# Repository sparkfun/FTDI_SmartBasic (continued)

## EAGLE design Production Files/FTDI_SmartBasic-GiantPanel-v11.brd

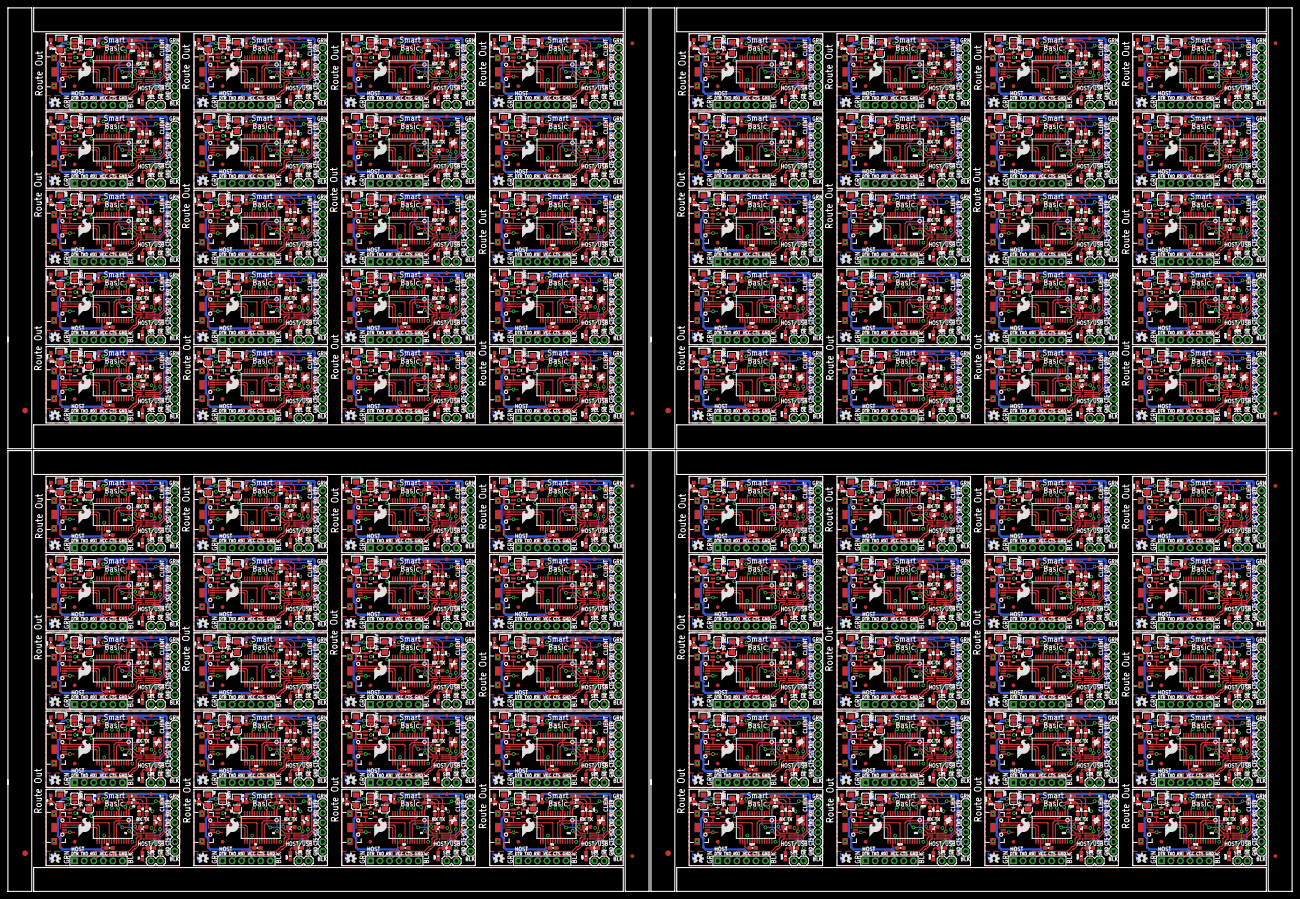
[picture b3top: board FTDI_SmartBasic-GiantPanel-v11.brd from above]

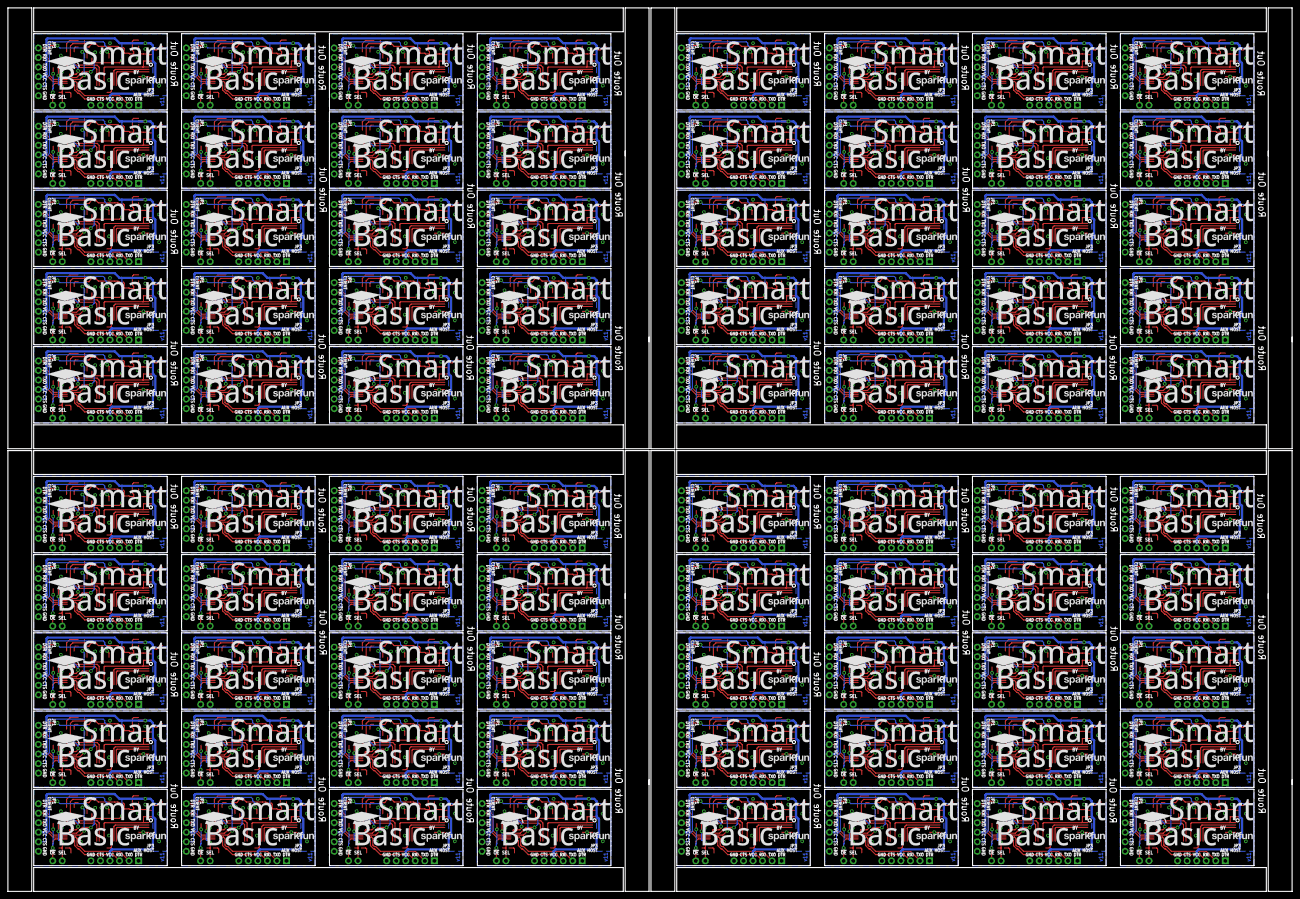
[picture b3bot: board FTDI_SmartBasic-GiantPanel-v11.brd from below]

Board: 2 copper layers, 341.9 x 235.2 mm, 2252 parts (160 on the bottom side), 1840 nets.

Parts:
C1, C3, C8, C11, C14, C17, C20, C23, C26, C29, C32, C35, C38, C41, C44, C47, C50, C53, C56, C59, C62, C65, C68, C71, C74, C77, C80, C83, C86, C89, C92, C95, C98, C101, C104, C107, C110, C113, C116, C119, C122, C125, C128, C131, C134, C137, C140, C143, C146, C149, C152, C155, C158, C161, C164, C167, C170, C173, C176, C179, C182, C185, C188, C191, C194, C197, C200, C203, C206, C209, C212, C215, C218, C221, C224, C227, C230, C233, C236, C239, C242, C245, C248, C251, C254, C257, C260, C263, C266, C269, C272, C275, C278, C281, C284, C287, C290, C293, C296, C299, C302, C305, C308, C311, C314, C317, C320, C323, C326, C329, C332, C335, C338, C341, C344, C347, C350, C353, C356, C359, C362, C365, C368, C371, C374, C377, C380, C383, C386, C389, C392, C395, C398, C401, C404, C407, C410, C413, C416, C419, C422, C425, C428, C431, C434, C437, C440, C443, C446, C449, C452, C455, C458, C461, C464, C467, C470, C473, C476, C479: 10uF; EIA3216
C2, C4, C5, C6, C7, C9, C10, C12, C13, C15, C16, C18, C19, C21, C22, C24, C25, C27, C28, C30, C31, C33, C34, C36, C37, C39, C40, C42, C43, C45, C46, C48, C49, C51, C52, C54, C55, C57, C58, C60, C61, C63, C64, C66, C67, C69, C70, C72, C73, C75, C76, C78, C79, C81, C82, C84, C85, C87, C88, C90, C91, C93, C94, C96, C97, C99, C100, C102, C103, C105, C106, C108, C109, C111, C112, C114, C115, C117, C118, C120, C121, C123, C124, C126, C127, C129, C130, C132, C133, C135, C136, C138, C139, C141, C142, C144, C145, C147, C148, C150, C151, C153, C154, C156, C157, C159, C160, C162, C163, C165, C166, C168, C169, C171, C172, C174, C175, C177, C178, C180, C181, C183, C184, C186, C187, C189, C190, C192, C193, C195, C196, C198, C199, C201, C202, C204, C205, C207, C208, C210, C211, C213, C214, C216, C217, C219, C220, C222, C223, C225, C226, C228, C229, C231, C232, C234, C235, C237, C238, C240, C241, C243, C244, C246, C247, C249, C250, C252, C253, C255, C256, C258, C259, C261, C262, C264, C265, C267, C268, C270, C271, C273, C274, C276, C277, C279, C280, C282, C283, C285, C286, C288, C289, C291, C292, C294, C295, C297, C298, C300, C301, C303, C304, C306, C307, C309, C310, C312, C313, C315, C316, C318, C319, C321, C322, C324, C325, C327, C328, C330, C331, C333, C334, C336, C337, C339, C340, C342, C343, C345, C346, C348, C349, C351, C352, C354, C355, C357, C358, C360, C361, C363, C364, C366, C367, C369, C370, C372, C373, C375, C376, C378, C379, C381, C382, C384, C385, C387, C388, C390, C391, C393, C394, C396, C397, C399, C400, C402, C403, C405, C406, C408, C409, C411, C412, C414, C415, C417, C418, C420, C421, C423, C424, C426, C427, C429, C430, C432, C433, C435, C436, C438, C439, C441, C442, C444, C445, C447, C448, C450, C451, C453, C454, C456, C457, C459, C460, C462, C463, C465, C466, C468, C469, C471, C472, C474, C475, C477, C478, C480: 0.1uF; 0603-CAP
CLIENT, CLIENT1, CLIENT2, CLIENT3, CLIENT4, CLIENT5, CLIENT6, CLIENT7, CLIENT8, CLIENT9, CLIENT10, CLIENT11, CLIENT12, CLIENT13, CLIENT14, CLIENT15, CLIENT16, CLIENT17, CLIENT18, CLIENT19, CLIENT20, CLIENT21, CLIENT22, CLIENT23, CLIENT24, CLIENT25, CLIENT26, CLIENT27, CLIENT28, CLIENT29, CLIENT30, CLIENT31, CLIENT32, CLIENT33, CLIENT34, CLIENT35, CLIENT36, CLIENT37, CLIENT38, CLIENT39, CLIENT40, CLIENT41, CLIENT42, CLIENT43, CLIENT44, CLIENT45, CLIENT46, CLIENT47, CLIENT48, CLIENT49, CLIENT50, CLIENT51, CLIENT52, CLIENT53, CLIENT54, CLIENT55, CLIENT56, CLIENT57, CLIENT58, CLIENT59, CLIENT60, CLIENT61, CLIENT62, CLIENT63, CLIENT64, CLIENT65, CLIENT66, CLIENT67, CLIENT68, CLIENT69, CLIENT70, CLIENT71, CLIENT72, CLIENT73, CLIENT74, CLIENT75, CLIENT76, CLIENT77, CLIENT78, CLIENT79: FTDI_BASIC
D1, D3, D4, D6, D7, D9, D10, D12, D13, D15, D16, D18, D19, D21, D22, D24, D25, D27, D28, D30, D31, D33, D34, D36, D37, D39, D40, D42, D43, D45, D46, D48, D49, D51, D52, D54, D55, D57, D58, D60, D61, D63, D64, D66, D67, D69, D70, D72, D73, D75, D76, D78, D79, D81, D82, D84, D85, D87, D88, D90, D91, D93, D94, D96, D97, D99, D100, D102, D103, D105, D106, D108, D109, D111, D112, D114, D115, D117, D118, D120, D121, D123, D124, D126, D127, D129, D130, D132, D133, D135, D136, D138, D139, D141, D142, D144, D145, D147, D148, D150, D151, D153, D154, D156, D157, D159, D160, D162, D163, D165, D166, D168, D169, D171, D172, D174, D175, D177, D178, D180, D181, D183, D184, D186, D187, D189, D190, D192, D193, D195, D196, D198, D199, D201, D202, D204, D205, D207, D208, D210, D211, D213, D214, D216, D217, D219, D220, D222, D223, D225, D226, D228, D229, D231, D232, D234, D235, D237, D238, D240: GREEN; LED-0603
D2, D5, D8, D11, D14, D17, D20, D23, D26, D29, D32, D35, D38, D41, D44, D47, D50, D53, D56, D59, D62, D65, D68, D71, D74, D77, D80, D83, D86, D89, D92, D95, D98, D101, D104, D107, D110, D113, D116, D119, D122, D125, D128, D131, D134, D137, D140, D143, D146, D149, D152, D155, D158, D161, D164, D167, D170, D173, D176, D179, D182, D185, D188, D191, D194, D197, D200, D203, D206, D209, D212, D215, D218, D221, D224, D227, D230, D233, D236, D239: RED; LED-0603
E$1, E$4, E$9, E$12: FIDUCIAL-1.5X3
E$2, E$3, E$5, E$6, E$7, E$8, E$10, E$11: FIDUCIAL-1X2
FID1, FID2, FID3, FID4, FID5, FID6, FID7, FID8, FID9, FID10, FID11, FID12, FID13, FID14, FID15, FID16, FID17, FID18, FID19, FID20, FID21, FID22, FID23, FID24, FID25, FID26, FID27, FID28, FID29, FID30, FID31, FID32, FID33, FID34, FID35, FID36, FID37, FID38, FID39, FID40, FID41, FID42, FID43, FID44, FID45, FID46, FID47, FID48, FID49, FID50, FID51, FID52, FID53, FID54, FID55, FID56, FID57, FID58, FID59, FID60, FID61, FID62, FID63, FID64, FID65, FID66, FID67, FID68, FID69, FID70, FID71, FID72, FID73, FID74, FID75, FID76, FID77, FID78, FID79, FID80, FID81, FID82, FID83, FID84, FID85, FID86, FID87, FID88, FID89, FID90, FID91, FID92, FID93, FID94, FID95, FID96, FID97, FID98, FID99, FID100, FID101, FID102, FID103, FID104, FID105, FID106, FID107, FID108, FID109, FID110, FID111, FID112, FID113, FID114, FID115, FID116, FID117, FID118, FID119, FID120, FID121, FID122, FID123, FID124, FID125, FID126, FID127, FID128, FID129, FID130, FID131, FID132, FID133, FID134, FID135, FID136, FID137, FID138, FID139, FID140, FID141, FID142, FID143, FID144, FID145, FID146, FID147, FID148, FID149, FID150, FID151, FID152, FID153, FID154, FID155, FID156, FID157, FID158, FID159, FID160: FIDUCIAL1X2; FIDUCIAL-1X2
HOST, HOST1, HOST2, HOST3, HOST4, HOST5, HOST6, HOST7, HOST8, HOST9, HOST10, HOST11, HOST12, HOST13, HOST14, HOST15, HOST16, HOST17, HOST18, HOST19, HOST20, HOST21, HOST22, HOST23, HOST24, HOST25, HOST26, HOST27, HOST28, HOST29, HOST30, HOST31, HOST32, HOST33, HOST34, HOST35, HOST36, HOST37, HOST38, HOST39, HOST40, HOST41, HOST42, HOST43, HOST44, HOST45, HOST46, HOST47, HOST48, HOST49, HOST50, HOST51, HOST52, HOST53, HOST54, HOST55, HOST56, HOST57, HOST58, HOST59, HOST60, HOST61, HOST62, HOST63, HOST64, HOST65, HOST66, HOST67, HOST68, HOST69, HOST70, HOST71, HOST72, HOST73, HOST74, HOST75, HOST76, HOST77, HOST78, HOST79: FTDI_DEVICE_SIDE
JP1, JP4, JP5, JP7, JP9, JP11, JP13, JP15, JP17, JP19, JP21, JP23, JP25, JP27, JP29, JP31, JP33, JP35, JP37, JP39, JP41, JP43, JP45, JP47, JP49, JP51, JP53, JP55, JP57, JP59, JP61, JP63, JP65, JP67, JP69, JP71, JP73, JP75, JP77, JP79, JP81, JP83, JP85, JP87, JP89, JP91, JP93, JP95, JP97, JP99, JP101, JP103, JP105, JP107, JP109, JP111, JP113, JP115, JP117, JP119, JP121, JP123, JP125, JP127, JP129, JP131, JP133, JP135, JP137, JP139, JP141, JP143, JP145, JP147, JP149, JP151, JP153, JP155, JP157, JP159: USB Micro B; USB-B-MICRO-SMD_V03
JP2, JP3, JP6, JP8, JP10, JP12, JP14, JP16, JP18, JP20, JP22, JP24, JP26, JP28, JP30, JP32, JP34, JP36, JP38, JP40, JP42, JP44, JP46, JP48, JP50, JP52, JP54, JP56, JP58, JP60, JP62, JP64, JP66, JP68, JP70, JP72, JP74, JP76, JP78, JP80, JP82, JP84, JP86, JP88, JP90, JP92, JP94, JP96, JP98, JP100, JP102, JP104, JP106, JP108, JP110, JP112, JP114, JP116, JP118, JP120, JP122, JP124, JP126, JP128, JP130, JP132, JP134, JP136, JP138, JP140, JP142, JP144, JP146, JP148, JP150, JP152, JP154, JP156, JP158, JP160: M02PTH; 1X02
LOGO1, LOGO4, LOGO7, LOGO10, LOGO13, LOGO16, LOGO19, LOGO22, LOGO25, LOGO28, LOGO31, LOGO34, LOGO37, LOGO40, LOGO43, LOGO46, LOGO49, LOGO52, LOGO55, LOGO58, LOGO61, LOGO64, LOGO67, LOGO70, LOGO73, LOGO76, LOGO79, LOGO82, LOGO85, LOGO88, LOGO91, LOGO94, LOGO97, LOGO100, LOGO103, LOGO106, LOGO109, LOGO112, LOGO115, LOGO118, LOGO121, LOGO124, LOGO127, LOGO130, LOGO133, LOGO136, LOGO139, LOGO142, LOGO145, LOGO148, LOGO151, LOGO154, LOGO157, LOGO160, LOGO163, LOGO166, LOGO169, LOGO172, LOGO175, LOGO178, LOGO181, LOGO184, LOGO187, LOGO190, LOGO193, LOGO196, LOGO199, LOGO202, LOGO205, LOGO208, LOGO211, LOGO214, LOGO217, LOGO220, LOGO223, LOGO226, LOGO229, LOGO232, LOGO235, LOGO238: SFE_LOGO_NAME.1_INCH; SFE_LOGO_NAME_.1
LOGO2, LOGO6, LOGO9, LOGO12, LOGO15, LOGO18, LOGO21, LOGO24, LOGO27, LOGO30, LOGO33, LOGO36, LOGO39, LOGO42, LOGO45, LOGO48, LOGO51, LOGO54, LOGO57, LOGO60, LOGO63, LOGO66, LOGO69, LOGO72, LOGO75, LOGO78, LOGO81, LOGO84, LOGO87, LOGO90, LOGO93, LOGO96, LOGO99, LOGO102, LOGO105, LOGO108, LOGO111, LOGO114, LOGO117, LOGO120, LOGO123, LOGO126, LOGO129, LOGO132, LOGO135, LOGO138, LOGO141, LOGO144, LOGO147, LOGO150, LOGO153, LOGO156, LOGO159, LOGO162, LOGO165, LOGO168, LOGO171, LOGO174, LOGO177, LOGO180, LOGO183, LOGO186, LOGO189, LOGO192, LOGO195, LOGO198, LOGO201, LOGO204, LOGO207, LOGO210, LOGO213, LOGO216, LOGO219, LOGO222, LOGO225, LOGO228, LOGO231, LOGO234, LOGO237, LOGO240: SFE_LOGO_FLAME.2_INCH; SFE_LOGO_FLAME_.2
LOGO3, LOGO5, LOGO8, LOGO11, LOGO14, LOGO17, LOGO20, LOGO23, LOGO26, LOGO29, LOGO32, LOGO35, LOGO38, LOGO41, LOGO44, LOGO47, LOGO50, LOGO53, LOGO56, LOGO59, LOGO62, LOGO65, LOGO68, LOGO71, LOGO74, LOGO77, LOGO80, LOGO83, LOGO86, LOGO89, LOGO92, LOGO95, LOGO98, LOGO101, LOGO104, LOGO107, LOGO110, LOGO113, LOGO116, LOGO119, LOGO122, LOGO125, LOGO128, LOGO131, LOGO134, LOGO137, LOGO140, LOGO143, LOGO146, LOGO149, LOGO152, LOGO155, LOGO158, LOGO161, LOGO164, LOGO167, LOGO170, LOGO173, LOGO176, LOGO179, LOGO182, LOGO185, LOGO188, LOGO191, LOGO194, LOGO197, LOGO200, LOGO203, LOGO206, LOGO209, LOGO212, LOGO215, LOGO218, LOGO221, LOGO224, LOGO227, LOGO230, LOGO233, LOGO236, LOGO239: OSHW-LOGOS; OSHW-LOGO-S
R1, R2, R3, R5, R6, R7, R9, R10, R11, R12, R14, R15, R16, R17, R19, R20, R21, R22, R24, R25, R26, R27, R29, R30, R31, R32, R34, R35, R36, R37, R39, R40, R41, R42, R44, R45, R46, R47, R49, R50, R51, R52, R54, R55, R56, R57, R59, R60, R61, R62, R64, R65, R66, R67, R69, R70, R71, R72, R74, R75, R76, R77, R79, R80, R81, R82, R84, R85, R86, R87, R89, R90, R91, R92, R94, R95, R96, R97, R99, R100, R101, R102, R104, R105, R106, R107, R109, R110, R111, R112, R114, R115, R116, R117, R119, R120, R121, R122, R124, R125, R126, R127, R129, R130, R131, R132, R134, R135, R136, R137, R139, R140, R141, R142, R144, R145, R146, R147, R149, R150, R151, R152, R154, R155, R156, R157, R159, R160, R161, R162, R164, R165, R166, R167, R169, R170, R171, R172, R174, R175, R176, R177, R179, R180, R181, R182, R184, R185, R186, R187, R189, R190, R191, R192, R194, R195, R196, R197, R199, R200, R201, R202, R204, R205, R206, R207, R209, R210, R211, R212, R214, R215, R216, R217, R219, R220, R221, R222, R224, R225, R226, R227, R229, R230, R231, R232, R234, R235, R236, R237, R239, R240, R241, R242, R244, R245, R246, R247, R249, R250, R251, R252, R254, R255, R256, R257, R259, R260, R261, R262, R264, R265, R266, R267, R269, R270, R271, R272, R274, R275, R276, R277, R279, R280, R281, R282, R284, R285, R286, R287, R289, R290, R291, R292, R294, R295, R296, R297, R299, R300, R301, R302, R304, R305, R306, R307, R309, R310, R311, R312, R314, R315, R316, R317, R319, R320, R321, R322, R324, R325, R326, R327, R329, R330, R331, R332, R334, R335, R336, R337, R339, R340, R341, R342, R344, R345, R346, R347, R349, R350, R351, R352, R354, R355, R356, R357, R359, R360, R361, R362, R364, R365, R366, R367, R369, R370, R371, R372, R374, R375, R376, R377, R379, R380, R381, R382, R384, R385, R386, R387, R389, R390, R391, R392, R394, R395, R396, R397, R399, R400: 1K; 0603-RES
R4, R8, R13, R18, R23, R28, R33, R38, R43, R48, R53, R58, R63, R68, R73, R78, R83, R88, R93, R98, R103, R108, R113, R118, R123, R128, R133, R138, R143, R148, R153, R158, R163, R168, R173, R178, R183, R188, R193, R198, R203, R208, R213, R218, R223, R228, R233, R238, R243, R248, R253, R258, R263, R268, R273, R278, R283, R288, R293, R298, R303, R308, R313, R318, R323, R328, R333, R338, R343, R348, R353, R358, R363, R368, R373, R378, R383, R388, R393, R398: 10K; 0603-RES
SJ1, SJ2, SJ3, SJ4, SJ5, SJ6, SJ7, SJ8, SJ9, SJ10, SJ11, SJ12, SJ13, SJ14, SJ15, SJ16, SJ17, SJ18, SJ19, SJ20, SJ21, SJ22, SJ23, SJ24, SJ25, SJ26, SJ27, SJ28, SJ29, SJ30, SJ31, SJ32, SJ33, SJ34, SJ35, SJ36, SJ37, SJ38, SJ39, SJ40, SJ41, SJ42, SJ43, SJ44, SJ45, SJ46, SJ47, SJ48, SJ49, SJ50, SJ51, SJ52, SJ53, SJ54, SJ55, SJ56, SJ57, SJ58, SJ59, SJ60, SJ61, SJ62, SJ63, SJ64, SJ65, SJ66, SJ67, SJ68, SJ69, SJ70, SJ71, SJ72, SJ73, SJ74, SJ75, SJ76, SJ77, SJ78, SJ79, SJ80: JUMPER-PAD-3-2OF3_NC_BY_PASTE; PAD-JUMPER-3-2OF3_NC_BY_PASTE_YES_SILK_FULL_BOX
U1, U5, U8, U11, U14, U17, U20, U23, U26, U29, U32, U35, U38, U41, U44, U47, U50, U53, U56, U59, U62, U65, U68, U71, U74, U77, U80, U83, U86, U89, U92, U95, U98, U101, U104, U107, U110, U113, U116, U119, U122, U125, U128, U131, U134, U137, U140, U143, U146, U149, U152, U155, U158, U161, U164, U167, U170, U173, U176, U179, U182, U185, U188, U191, U194, U197, U200, U203, U206, U209, U212, U215, U218, U221, U224, U227, U230, U233, U236, U239: FT232RLSSOP; SSOP28DB
U2, U6, U9, U12, U15, U18, U21, U24, U27, U30, U33, U36, U39, U42, U45, U48, U51, U54, U57, U60, U63, U66, U69, U72, U75, U78, U81, U84, U87, U90, U93, U96, U99, U102, U105, U108, U111, U114, U117, U120, U123, U126, U129, U132, U135, U138, U141, U144, U147, U150, U153, U156, U159, U162, U165, U168, U171, U174, U177, U180, U183, U186, U189, U192, U195, U198, U201, U204, U207, U210, U213, U216, U219, U222, U225, U228, U231, U234, U237, U240: MIC5219 3.3V; SOT23-5
U3, U4, U7, U10, U13, U16, U19, U22, U25, U28, U31, U34, U37, U40, U43, U46, U49, U52, U55, U58, U61, U64, U67, U70, U73, U76, U79, U82, U85, U88, U91, U94, U97, U100, U103, U106, U109, U112, U115, U118, U121, U124, U127, U130, U133, U136, U139, U142, U145, U148, U151, U154, U157, U160, U163, U166, U169, U172, U175, U178, U181, U184, U187, U190, U193, U196, U199, U202, U205, U208, U211, U214, U217, U220, U223, U226, U229, U232, U235, U238: TS3USB221A; QFN-10-RSE
U$1, U$2, U$3, U$4, U$5, U$6, U$7, U$8, U$9, U$10, U$11, U$12, U$13, U$14, U$15, U$16, U$17, U$18, U$19, U$20, U$21, U$22, U$23, U$24, U$25, U$26, U$27, U$28, U$29, U$30, U$31, U$32, U$33, U$34, U$35, U$36, U$37, U$38, U$39, U$40, U$41, U$42, U$43, U$44, U$45, U$46, U$47, U$48, U$49, U$50, U$51, U$52, U$53, U$54, U$55, U$56, U$57, U$58, U$59, U$60, U$61, U$62, U$63, U$64, U$65, U$66, U$67, U$68, U$69, U$70, U$71, U$72, U$73, U$74, U$75, U$76, U$77, U$78, U$79, U$80: SMART_BASIC_LOGO

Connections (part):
3.3V: C3.A, C5.1, C6.1, R1.2, R2.2, SJ1.1, U2.5, U3.10
3.3V1: C8.A, C10.1, C12.1, R6.2, R7.2, SJ2.1, U4.10, U6.5
3.3V2: C14.A, C16.1, C18.1, R11.2, R12.2, SJ3.1, U7.10, U9.5
3.3V3: C20.A, C22.1, C24.1, R16.2, R17.2, SJ4.1, U10.10, U12.5
3.3V4: C26.A, C28.1, C30.1, R21.2, R22.2, SJ5.1, U13.10, U15.5
3.3V5: C32.A, C34.1, C36.1, R26.2, R27.2, SJ6.1, U16.10, U18.5
3.3V6: C38.A, C40.1, C42.1, R31.2, R32.2, SJ7.1, U19.10, U21.5
3.3V7: C44.A, C46.1, C48.1, R36.2, R37.2, SJ8.1, U22.10, U24.5
3.3V8: C50.A, C52.1, C54.1, R41.2, R42.2, SJ9.1, U25.10, U27.5
3.3V9: C56.A, C58.1, C60.1, R46.2, R47.2, SJ10.1, U28.10, U30.5
3.3V10: C62.A, C64.1, C66.1, R51.2, R52.2, SJ11.1, U31.10, U33.5
3.3V11: C68.A, C70.1, C72.1, R56.2, R57.2, SJ12.1, U34.10, U36.5
3.3V12: C74.A, C76.1, C78.1, R61.2, R62.2, SJ13.1, U37.10, U39.5
3.3V13: C80.A, C82.1, C84.1, R66.2, R67.2, SJ14.1, U40.10, U42.5
3.3V14: C86.A, C88.1, C90.1, R71.2, R72.2, SJ15.1, U43.10, U45.5
3.3V15: C92.A, C94.1, C96.1, R76.2, R77.2, SJ16.1, U46.10, U48.5
3.3V16: C98.A, C100.1, C102.1, R81.2, R82.2, SJ17.1, U49.10, U51.5
3.3V17: C104.A, C106.1, C108.1, R86.2, R87.2, SJ18.1, U52.10, U54.5
3.3V18: C110.A, C112.1, C114.1, R91.2, R92.2, SJ19.1, U55.10, U57.5
3.3V19: C116.A, C118.1, C120.1, R96.2, R97.2, SJ20.1, U58.10, U60.5
3.3V20: C122.A, C124.1, C126.1, R101.2, R102.2, SJ21.1, U61.10, U63.5
3.3V21: C128.A, C130.1, C132.1, R106.2, R107.2, SJ22.1, U64.10, U66.5
3.3V22: C134.A, C136.1, C138.1, R111.2, R112.2, SJ23.1, U67.10, U69.5
3.3V23: C140.A, C142.1, C144.1, R116.2, R117.2, SJ24.1, U70.10, U72.5
3.3V24: C146.A, C148.1, C150.1, R121.2, R122.2, SJ25.1, U73.10, U75.5
3.3V25: C152.A, C154.1, C156.1, R126.2, R127.2, SJ26.1, U76.10, U78.5
3.3V26: C158.A, C160.1, C162.1, R131.2, R132.2, SJ27.1, U79.10, U81.5
3.3V27: C164.A, C166.1, C168.1, R136.2, R137.2, SJ28.1, U82.10, U84.5
3.3V28: C170.A, C172.1, C174.1, R141.2, R142.2, SJ29.1, U85.10, U87.5
3.3V29: C176.A, C178.1, C180.1, R146.2, R147.2, SJ30.1, U88.10, U90.5
3.3V30: C182.A, C184.1, C186.1, R151.2, R152.2, SJ31.1, U91.10, U93.5
3.3V31: C188.A, C190.1, C192.1, R156.2, R157.2, SJ32.1, U94.10, U96.5
3.3V32: C194.A, C196.1, C198.1, R161.2, R162.2, SJ33.1, U97.10, U99.5
3.3V33: C200.A, C202.1, C204.1, R166.2, R167.2, SJ34.1, U100.10, U102.5
3.3V34: C206.A, C208.1, C210.1, R171.2, R172.2, SJ35.1, U103.10, U105.5
3.3V35: C212.A, C214.1, C216.1, R176.2, R177.2, SJ36.1, U106.10, U108.5
3.3V36: C218.A, C220.1, C222.1, R181.2, R182.2, SJ37.1, U109.10, U111.5
3.3V37: C224.A, C226.1, C228.1, R186.2, R187.2, SJ38.1, U112.10, U114.5
3.3V38: C230.A, C232.1, C234.1, R191.2, R192.2, SJ39.1, U115.10, U117.5
3.3V39: C236.A, C238.1, C240.1, R196.2, R197.2, SJ40.1, U118.10, U120.5
3.3V40: C242.A, C244.1, C246.1, R201.2, R202.2, SJ41.1, U121.10, U123.5
3.3V41: C248.A, C250.1, C252.1, R206.2, R207.2, SJ42.1, U124.10, U126.5
3.3V42: C254.A, C256.1, C258.1, R211.2, R212.2, SJ43.1, U127.10, U129.5
3.3V43: C260.A, C262.1, C264.1, R216.2, R217.2, SJ44.1, U130.10, U132.5
3.3V44: C266.A, C268.1, C270.1, R221.2, R222.2, SJ45.1, U133.10, U135.5
3.3V45: C272.A, C274.1, C276.1, R226.2, R227.2, SJ46.1, U136.10, U138.5
3.3V46: C278.A, C280.1, C282.1, R231.2, R232.2, SJ47.1, U139.10, U141.5
3.3V47: C284.A, C286.1, C288.1, R236.2, R237.2, SJ48.1, U142.10, U144.5
3.3V48: C290.A, C292.1, C294.1, R241.2, R242.2, SJ49.1, U145.10, U147.5
3.3V49: C296.A, C298.1, C300.1, R246.2, R247.2, SJ50.1, U148.10, U150.5
3.3V50: C302.A, C304.1, C306.1, R251.2, R252.2, SJ51.1, U151.10, U153.5
3.3V51: C308.A, C310.1, C312.1, R256.2, R257.2, SJ52.1, U154.10, U156.5
3.3V52: C314.A, C316.1, C318.1, R261.2, R262.2, SJ53.1, U157.10, U159.5
3.3V53: C320.A, C322.1, C324.1, R266.2, R267.2, SJ54.1, U160.10, U162.5
3.3V54: C326.A, C328.1, C330.1, R271.2, R272.2, SJ55.1, U163.10, U165.5
3.3V55: C332.A, C334.1, C336.1, R276.2, R277.2, SJ56.1, U166.10, U168.5
3.3V56: C338.A, C340.1, C342.1, R281.2, R282.2, SJ57.1, U169.10, U171.5
3.3V57: C344.A, C346.1, C348.1, R286.2, R287.2, SJ58.1, U172.10, U174.5
3.3V58: C350.A, C352.1, C354.1, R291.2, R292.2, SJ59.1, U175.10, U177.5
3.3V59: C356.A, C358.1, C360.1, R296.2, R297.2, SJ60.1, U178.10, U180.5
3.3V60: C362.A, C364.1, C366.1, R301.2, R302.2, SJ61.1, U181.10, U183.5
3.3V61: C368.A, C370.1, C372.1, R306.2, R307.2, SJ62.1, U184.10, U186.5
3.3V62: C374.A, C376.1, C378.1, R311.2, R312.2, SJ63.1, U187.10, U189.5
3.3V63: C380.A, C382.1, C384.1, R316.2, R317.2, SJ64.1, U190.10, U192.5
3.3V64: C386.A, C388.1, C390.1, R321.2, R322.2, SJ65.1, U193.10, U195.5
3.3V65: C392.A, C394.1, C396.1, R326.2, R327.2, SJ66.1, U196.10, U198.5
3.3V66: C398.A, C400.1, C402.1, R331.2, R332.2, SJ67.1, U199.10, U201.5
3.3V67: C404.A, C406.1, C408.1, R336.2, R337.2, SJ68.1, U202.10, U204.5
3.3V68: C410.A, C412.1, C414.1, R341.2, R342.2, SJ69.1, U205.10, U207.5
3.3V69: C416.A, C418.1, C420.1, R346.2, R347.2, SJ70.1, U208.10, U210.5
3.3V70: C422.A, C424.1, C426.1, R351.2, R352.2, SJ71.1, U211.10, U213.5
3.3V71: C428.A, C430.1, C432.1, R356.2, R357.2, SJ72.1, U214.10, U216.5
3.3V72: C434.A, C436.1, C438.1, R361.2, R362.2, SJ73.1, U217.10, U219.5
3.3V73: C440.A, C442.1, C444.1, R366.2, R367.2, SJ74.1, U220.10, U222.5
3.3V74: C446.A, C448.1, C450.1, R371.2, R372.2, SJ75.1, U223.10, U225.5
3.3V75: C452.A, C454.1, C456.1, R376.2, R377.2, SJ76.1, U226.10, U228.5
3.3V76: C458.A, C460.1, C462.1, R381.2, R382.2, SJ77.1, U229.10, U231.5
3.3V77: C464.A, C466.1, C468.1, R386.2, R387.2, SJ78.1, U232.10, U234.5
3.3V78: C470.A, C472.1, C474.1, R391.2, R392.2, SJ79.1, U235.10, U237.5
3.3V79: C476.A, C478.1, C480.1, R396.2, R397.2, SJ80.1, U238.10, U240.5
5V: C1.A, C2.1, JP4.VBUS1, SJ1.3, U1.20, U2.1, U2.3
5V1: C7.1, C11.A, JP1.VBUS1, SJ2.3, U5.20, U6.1, U6.3
5V2: C13.1, C17.A, JP5.VBUS1, SJ3.3, U8.20, U9.1, U9.3
5V3: C19.1, C23.A, JP7.VBUS1, SJ4.3, U11.20, U12.1, U12.3
5V4: C25.1, C29.A, JP9.VBUS1, SJ5.3, U14.20, U15.1, U15.3
5V5: C31.1, C35.A, JP11.VBUS1, SJ6.3, U17.20, U18.1, U18.3
5V6: C37.1, C41.A, JP13.VBUS1, SJ7.3, U20.20, U21.1, U21.3
5V7: C43.1, C47.A, JP15.VBUS1, SJ8.3, U23.20, U24.1, U24.3
5V8: C49.1, C53.A, JP17.VBUS1, SJ9.3, U26.20, U27.1, U27.3
5V9: C55.1, C59.A, JP19.VBUS1, SJ10.3, U29.20, U30.1, U30.3
5V10: C61.1, C65.A, JP21.VBUS1, SJ11.3, U32.20, U33.1, U33.3
5V11: C67.1, C71.A, JP23.VBUS1, SJ12.3, U35.20, U36.1, U36.3
5V12: C73.1, C77.A, JP25.VBUS1, SJ13.3, U38.20, U39.1, U39.3
5V13: C79.1, C83.A, JP27.VBUS1, SJ14.3, U41.20, U42.1, U42.3
5V14: C85.1, C89.A, JP29.VBUS1, SJ15.3, U44.20, U45.1, U45.3
5V15: C91.1, C95.A, JP31.VBUS1, SJ16.3, U47.20, U48.1, U48.3
5V16: C97.1, C101.A, JP33.VBUS1, SJ17.3, U50.20, U51.1, U51.3
5V17: C103.1, C107.A, JP35.VBUS1, SJ18.3, U53.20, U54.1, U54.3
5V18: C109.1, C113.A, JP37.VBUS1, SJ19.3, U56.20, U57.1, U57.3
5V19: C115.1, C119.A, JP39.VBUS1, SJ20.3, U59.20, U60.1, U60.3
5V20: C121.1, C125.A, JP41.VBUS1, SJ21.3, U62.20, U63.1, U63.3
5V21: C127.1, C131.A, JP43.VBUS1, SJ22.3, U65.20, U66.1, U66.3
5V22: C133.1, C137.A, JP45.VBUS1, SJ23.3, U68.20, U69.1, U69.3
5V23: C139.1, C143.A, JP47.VBUS1, SJ24.3, U71.20, U72.1, U72.3
5V24: C145.1, C149.A, JP49.VBUS1, SJ25.3, U74.20, U75.1, U75.3
5V25: C151.1, C155.A, JP51.VBUS1, SJ26.3, U77.20, U78.1, U78.3
5V26: C157.1, C161.A, JP53.VBUS1, SJ27.3, U80.20, U81.1, U81.3
5V27: C163.1, C167.A, JP55.VBUS1, SJ28.3, U83.20, U84.1, U84.3
5V28: C169.1, C173.A, JP57.VBUS1, SJ29.3, U86.20, U87.1, U87.3
5V29: C175.1, C179.A, JP59.VBUS1, SJ30.3, U89.20, U90.1, U90.3
5V30: C181.1, C185.A, JP61.VBUS1, SJ31.3, U92.20, U93.1, U93.3
5V31: C187.1, C191.A, JP63.VBUS1, SJ32.3, U95.20, U96.1, U96.3
5V32: C193.1, C197.A, JP65.VBUS1, SJ33.3, U98.20, U99.1, U99.3
5V33: C199.1, C203.A, JP67.VBUS1, SJ34.3, U101.20, U102.1, U102.3
5V34: C205.1, C209.A, JP69.VBUS1, SJ35.3, U104.20, U105.1, U105.3
5V35: C211.1, C215.A, JP71.VBUS1, SJ36.3, U107.20, U108.1, U108.3
5V36: C217.1, C221.A, JP73.VBUS1, SJ37.3, U110.20, U111.1, U111.3
5V37: C223.1, C227.A, JP75.VBUS1, SJ38.3, U113.20, U114.1, U114.3
5V38: C229.1, C233.A, JP77.VBUS1, SJ39.3, U116.20, U117.1, U117.3
5V39: C235.1, C239.A, JP79.VBUS1, SJ40.3, U119.20, U120.1, U120.3
5V40: C241.1, C245.A, JP81.VBUS1, SJ41.3, U122.20, U123.1, U123.3
5V41: C247.1, C251.A, JP83.VBUS1, SJ42.3, U125.20, U126.1, U126.3
5V42: C253.1, C257.A, JP85.VBUS1, SJ43.3, U128.20, U129.1, U129.3
5V43: C259.1, C263.A, JP87.VBUS1, SJ44.3, U131.20, U132.1, U132.3
5V44: C265.1, C269.A, JP89.VBUS1, SJ45.3, U134.20, U135.1, U135.3
5V45: C271.1, C275.A, JP91.VBUS1, SJ46.3, U137.20, U138.1, U138.3
5V46: C277.1, C281.A, JP93.VBUS1, SJ47.3, U140.20, U141.1, U141.3
5V47: C283.1, C287.A, JP95.VBUS1, SJ48.3, U143.20, U144.1, U144.3
5V48: C289.1, C293.A, JP97.VBUS1, SJ49.3, U146.20, U147.1, U147.3
5V49: C295.1, C299.A, JP99.VBUS1, SJ50.3, U149.20, U150.1, U150.3
5V50: C301.1, C305.A, JP101.VBUS1, SJ51.3, U152.20, U153.1, U153.3
5V51: C307.1, C311.A, JP103.VBUS1, SJ52.3, U155.20, U156.1, U156.3
5V52: C313.1, C317.A, JP105.VBUS1, SJ53.3, U158.20, U159.1, U159.3
5V53: C319.1, C323.A, JP107.VBUS1, SJ54.3, U161.20, U162.1, U162.3
5V54: C325.1, C329.A, JP109.VBUS1, SJ55.3, U164.20, U165.1, U165.3
5V55: C331.1, C335.A, JP111.VBUS1, SJ56.3, U167.20, U168.1, U168.3
5V56: C337.1, C341.A, JP113.VBUS1, SJ57.3, U170.20, U171.1, U171.3
5V57: C343.1, C347.A, JP115.VBUS1, SJ58.3, U173.20, U174.1, U174.3
5V58: C349.1, C353.A, JP117.VBUS1, SJ59.3, U176.20, U177.1, U177.3
5V59: C355.1, C359.A, JP119.VBUS1, SJ60.3, U179.20, U180.1, U180.3
5V60: C361.1, C365.A, JP121.VBUS1, SJ61.3, U182.20, U183.1, U183.3
5V61: C367.1, C371.A, JP123.VBUS1, SJ62.3, U185.20, U186.1, U186.3
5V62: C373.1, C377.A, JP125.VBUS1, SJ63.3, U188.20, U189.1, U189.3
5V63: C379.1, C383.A, JP127.VBUS1, SJ64.3, U191.20, U192.1, U192.3
5V64: C385.1, C389.A, JP129.VBUS1, SJ65.3, U194.20, U195.1, U195.3
5V65: C391.1, C395.A, JP131.VBUS1, SJ66.3, U197.20, U198.1, U198.3
5V66: C397.1, C401.A, JP133.VBUS1, SJ67.3, U200.20, U201.1, U201.3
5V67: C403.1, C407.A, JP135.VBUS1, SJ68.3, U203.20, U204.1, U204.3
5V68: C409.1, C413.A, JP137.VBUS1, SJ69.3, U206.20, U207.1, U207.3
5V69: C415.1, C419.A, JP139.VBUS1, SJ70.3, U209.20, U210.1, U210.3
5V70: C421.1, C425.A, JP141.VBUS1, SJ71.3, U212.20, U213.1, U213.3
5V71: C427.1, C431.A, JP143.VBUS1, SJ72.3, U215.20, U216.1, U216.3
5V72: C433.1, C437.A, JP145.VBUS1, SJ73.3, U218.20, U219.1, U219.3
5V73: C439.1, C443.A, JP147.VBUS1, SJ74.3, U221.20, U222.1, U222.3
5V74: C445.1, C449.A, JP149.VBUS1, SJ75.3, U224.20, U225.1, U225.3
5V75: C451.1, C455.A, JP151.VBUS1, SJ76.3, U227.20, U228.1, U228.3
5V76: C457.1, C461.A, JP153.VBUS1, SJ77.3, U230.20, U231.1, U231.3
5V77: C463.1, C467.A, JP155.VBUS1, SJ78.3, U233.20, U234.1, U234.3
5V78: C469.1, C473.A, JP157.VBUS1, SJ79.3, U236.20, U237.1, U237.3
5V79: C475.1, C479.A, JP159.VBUS1, SJ80.3, U239.20, U240.1, U240.3
!OE: JP2.1, R4.1, U3.6
!OE1: JP3.1, R8.1, U4.6
!OE2: JP6.1, R13.1, U7.6
!OE3: JP8.1, R18.1, U10.6
!OE4: JP10.1, R23.1, U13.6
!OE5: JP12.1, R28.1, U16.6
!OE6: JP14.1, R33.1, U19.6
!OE7: JP16.1, R38.1, U22.6
!OE8: JP18.1, R43.1, U25.6
!OE9: JP20.1, R48.1, U28.6
!OE10: JP22.1, R53.1, U31.6
!OE11: JP24.1, R58.1, U34.6
!OE12: JP26.1, R63.1, U37.6
!OE13: JP28.1, R68.1, U40.6
!OE14: JP30.1, R73.1, U43.6
!OE15: JP32.1, R78.1, U46.6
!OE16: JP34.1, R83.1, U49.6
!OE17: JP36.1, R88.1, U52.6
!OE18: JP38.1, R93.1, U55.6
!OE19: JP40.1, R98.1, U58.6
!OE20: JP42.1, R103.1, U61.6
!OE21: JP44.1, R108.1, U64.6
!OE22: JP46.1, R113.1, U67.6
!OE23: JP48.1, R118.1, U70.6
!OE24: JP50.1, R123.1, U73.6
!OE25: JP52.1, R128.1, U76.6
!OE26: JP54.1, R133.1, U79.6
!OE27: JP56.1, R138.1, U82.6
!OE28: JP58.1, R143.1, U85.6
!OE29: JP60.1, R148.1, U88.6
!OE30: JP62.1, R153.1, U91.6
!OE31: JP64.1, R158.1, U94.6
!OE32: JP66.1, R163.1, U97.6
!OE33: JP68.1, R168.1, U100.6
!OE34: JP70.1, R173.1, U103.6
!OE35: JP72.1, R178.1, U106.6
!OE36: JP74.1, R183.1, U109.6
!OE37: JP76.1, R188.1, U112.6
!OE38: JP78.1, R193.1, U115.6
!OE39: JP80.1, R198.1, U118.6
!OE40: JP82.1, R203.1, U121.6
!OE41: JP84.1, R208.1, U124.6
!OE42: JP86.1, R213.1, U127.6
!OE43: JP88.1, R218.1, U130.6
!OE44: JP90.1, R223.1, U133.6
!OE45: JP92.1, R228.1, U136.6
!OE46: JP94.1, R233.1, U139.6
!OE47: JP96.1, R238.1, U142.6
!OE48: JP98.1, R243.1, U145.6
!OE49: JP100.1, R248.1, U148.6
!OE50: JP102.1, R253.1, U151.6
!OE51: JP104.1, R258.1, U154.6
!OE52: JP106.1, R263.1, U157.6
!OE53: JP108.1, R268.1, U160.6
!OE54: JP110.1, R273.1, U163.6
!OE55: JP112.1, R278.1, U166.6
!OE56: JP114.1, R283.1, U169.6
!OE57: JP116.1, R288.1, U172.6
!OE58: JP118.1, R293.1, U175.6
!OE59: JP120.1, R298.1, U178.6
!OE60: JP122.1, R303.1, U181.6
!OE61: JP124.1, R308.1, U184.6
!OE62: JP126.1, R313.1, U187.6
!OE63: JP128.1, R318.1, U190.6
!OE64: JP130.1, R323.1, U193.6
!OE65: JP132.1, R328.1, U196.6
!OE66: JP134.1, R333.1, U199.6
!OE67: JP136.1, R338.1, U202.6
!OE68: JP138.1, R343.1, U205.6
!OE69: JP140.1, R348.1, U208.6
!OE70: JP142.1, R353.1, U211.6
!OE71: JP144.1, R358.1, U214.6
!OE72: JP146.1, R363.1, U217.6
!OE73: JP148.1, R368.1, U220.6
!OE74: JP150.1, R373.1, U223.6
!OE75: JP152.1, R378.1, U226.6
!OE76: JP154.1, R383.1, U229.6
!OE77: JP156.1, R388.1, U232.6
!OE78: JP158.1, R393.1, U235.6
!OE79: JP160.1, R398.1, U238.6
CTS: CLIENT.CTS, U1.11
CTS1: CLIENT1.CTS, U5.11
CTS2: CLIENT2.CTS, U8.11
CTS3: CLIENT3.CTS, U11.11
CTS4: CLIENT4.CTS, U14.11
CTS5: CLIENT5.CTS, U17.11
CTS6: CLIENT6.CTS, U20.11
CTS7: CLIENT7.CTS, U23.11
CTS8: CLIENT8.CTS, U26.11
CTS9: CLIENT9.CTS, U29.11
CTS10: CLIENT10.CTS, U32.11
CTS11: CLIENT11.CTS, U35.11
CTS12: CLIENT12.CTS, U38.11
CTS13: CLIENT13.CTS, U41.11
CTS14: CLIENT14.CTS, U44.11
CTS15: CLIENT15.CTS, U47.11
CTS16: CLIENT16.CTS, U50.11
CTS17: CLIENT17.CTS, U53.11
CTS18: CLIENT18.CTS, U56.11
CTS19: CLIENT19.CTS, U59.11
CTS20: CLIENT20.CTS, U62.11
CTS21: CLIENT21.CTS, U65.11
CTS22: CLIENT22.CTS, U68.11
CTS23: CLIENT23.CTS, U71.11
CTS24: CLIENT24.CTS, U74.11
CTS25: CLIENT25.CTS, U77.11
CTS26: CLIENT26.CTS, U80.11
CTS27: CLIENT27.CTS, U83.11
CTS28: CLIENT28.CTS, U86.11
CTS29: CLIENT29.CTS, U89.11
CTS30: CLIENT30.CTS, U92.11
CTS31: CLIENT31.CTS, U95.11
CTS32: CLIENT32.CTS, U98.11
CTS33: CLIENT33.CTS, U101.11
CTS34: CLIENT34.CTS, U104.11
CTS35: CLIENT35.CTS, U107.11
CTS36: CLIENT36.CTS, U110.11
CTS37: CLIENT37.CTS, U113.11
CTS38: CLIENT38.CTS, U116.11
CTS39: CLIENT39.CTS, U119.11
CTS40: CLIENT40.CTS, U122.11
CTS41: CLIENT41.CTS, U125.11
CTS42: CLIENT42.CTS, U128.11
CTS43: CLIENT43.CTS, U131.11
CTS44: CLIENT44.CTS, U134.11
CTS45: CLIENT45.CTS, U137.11
CTS46: CLIENT46.CTS, U140.11
CTS47: CLIENT47.CTS, U143.11
CTS48: CLIENT48.CTS, U146.11
CTS49: CLIENT49.CTS, U149.11
CTS50: CLIENT50.CTS, U152.11
CTS51: CLIENT51.CTS, U155.11
CTS52: CLIENT52.CTS, U158.11
CTS53: CLIENT53.CTS, U161.11
CTS54: CLIENT54.CTS, U164.11
CTS55: CLIENT55.CTS, U167.11
CTS56: CLIENT56.CTS, U170.11
CTS57: CLIENT57.CTS, U173.11
CTS58: CLIENT58.CTS, U176.11
CTS59: CLIENT59.CTS, U179.11
CTS60: CLIENT60.CTS, U182.11
CTS61: CLIENT61.CTS, U185.11
CTS62: CLIENT62.CTS, U188.11
CTS63: CLIENT63.CTS, U191.11
CTS64: CLIENT64.CTS, U194.11
CTS65: CLIENT65.CTS, U197.11
CTS66: CLIENT66.CTS, U200.11
CTS67: CLIENT67.CTS, U203.11
CTS68: CLIENT68.CTS, U206.11
CTS69: CLIENT69.CTS, U209.11
CTS70: CLIENT70.CTS, U212.11
CTS71: CLIENT71.CTS, U215.11
CTS72: CLIENT72.CTS, U218.11
CTS73: CLIENT73.CTS, U221.11
CTS74: CLIENT74.CTS, U224.11
CTS75: CLIENT75.CTS, U227.11
CTS76: CLIENT76.CTS, U230.11
CTS77: CLIENT77.CTS, U233.11
CTS78: CLIENT78.CTS, U236.11
CTS79: CLIENT79.CTS, U239.11
DTR: CLIENT.DTR, U1.2
DTR1: CLIENT1.DTR, U5.2
DTR2: CLIENT2.DTR, U8.2
DTR3: CLIENT3.DTR, U11.2
DTR4: CLIENT4.DTR, U14.2
DTR5: CLIENT5.DTR, U17.2
DTR6: CLIENT6.DTR, U20.2
DTR7: CLIENT7.DTR, U23.2
DTR8: CLIENT8.DTR, U26.2
DTR9: CLIENT9.DTR, U29.2
DTR10: CLIENT10.DTR, U32.2
DTR11: CLIENT11.DTR, U35.2
DTR12: CLIENT12.DTR, U38.2
DTR13: CLIENT13.DTR, U41.2
DTR14: CLIENT14.DTR, U44.2
DTR15: CLIENT15.DTR, U47.2
DTR16: CLIENT16.DTR, U50.2
DTR17: CLIENT17.DTR, U53.2
DTR18: CLIENT18.DTR, U56.2
DTR19: CLIENT19.DTR, U59.2
DTR20: CLIENT20.DTR, U62.2
DTR21: CLIENT21.DTR, U65.2
DTR22: CLIENT22.DTR, U68.2
DTR23: CLIENT23.DTR, U71.2
DTR24: CLIENT24.DTR, U74.2
DTR25: CLIENT25.DTR, U77.2
DTR26: CLIENT26.DTR, U80.2
DTR27: CLIENT27.DTR, U83.2
DTR28: CLIENT28.DTR, U86.2
DTR29: CLIENT29.DTR, U89.2
DTR30: CLIENT30.DTR, U92.2
DTR31: CLIENT31.DTR, U95.2
DTR32: CLIENT32.DTR, U98.2
DTR33: CLIENT33.DTR, U101.2
DTR34: CLIENT34.DTR, U104.2
DTR35: CLIENT35.DTR, U107.2
DTR36: CLIENT36.DTR, U110.2
DTR37: CLIENT37.DTR, U113.2
DTR38: CLIENT38.DTR, U116.2
DTR39: CLIENT39.DTR, U119.2
DTR40: CLIENT40.DTR, U122.2
DTR41: CLIENT41.DTR, U125.2
DTR42: CLIENT42.DTR, U128.2
DTR43: CLIENT43.DTR, U131.2
DTR44: CLIENT44.DTR, U134.2
DTR45: CLIENT45.DTR, U137.2
DTR46: CLIENT46.DTR, U140.2
DTR47: CLIENT47.DTR, U143.2
DTR48: CLIENT48.DTR, U146.2
DTR49: CLIENT49.DTR, U149.2
DTR50: CLIENT50.DTR, U152.2
DTR51: CLIENT51.DTR, U155.2
DTR52: CLIENT52.DTR, U158.2
DTR53: CLIENT53.DTR, U161.2
DTR54: CLIENT54.DTR, U164.2
DTR55: CLIENT55.DTR, U167.2
DTR56: CLIENT56.DTR, U170.2
DTR57: CLIENT57.DTR, U173.2
DTR58: CLIENT58.DTR, U176.2
DTR59: CLIENT59.DTR, U179.2
DTR60: CLIENT60.DTR, U182.2
DTR61: CLIENT61.DTR, U185.2
DTR62: CLIENT62.DTR, U188.2
DTR63: CLIENT63.DTR, U191.2
DTR64: CLIENT64.DTR, U194.2
DTR65: CLIENT65.DTR, U197.2
DTR66: CLIENT66.DTR, U200.2
DTR67: CLIENT67.DTR, U203.2
DTR68: CLIENT68.DTR, U206.2
DTR69: CLIENT69.DTR, U209.2
DTR70: CLIENT70.DTR, U212.2
DTR71: CLIENT71.DTR, U215.2
DTR72: CLIENT72.DTR, U218.2
DTR73: CLIENT73.DTR, U221.2
DTR74: CLIENT74.DTR, U224.2
DTR75: CLIENT75.DTR, U227.2
DTR76: CLIENT76.DTR, U230.2
DTR77: CLIENT77.DTR, U233.2
DTR78: CLIENT78.DTR, U236.2
DTR79: CLIENT79.DTR, U239.2
GND: C1.C, C2.2, C3.C, C4.2, C5.2, C6.2, CLIENT.GND, HOST.P$6, JP4.GND1, R3.1, R4.2, R5.1, U1.7, U1.18, U1.21, U1.25, U1.26, U2.2, U3.5
GND1: C7.2, C8.C, C9.2, C10.2, C11.C, C12.2, CLIENT1.GND, HOST1.P$6, JP1.GND1, R8.2, R9.1, R10.1, U4.5, U5.7, U5.18, U5.21, U5.25, U5.26, U6.2
GND2: C13.2, C14.C, C15.2, C16.2, C17.C, C18.2, CLIENT2.GND, HOST2.P$6, JP5.GND1, R13.2, R14.1, R15.1, U7.5, U8.7, U8.18, U8.21, U8.25, U8.26, U9.2
GND3: C19.2, C20.C, C21.2, C22.2, C23.C, C24.2, CLIENT3.GND, HOST3.P$6, JP7.GND1, R18.2, R19.1, R20.1, U10.5, U11.7, U11.18, U11.21, U11.25, U11.26, U12.2
GND4: C25.2, C26.C, C27.2, C28.2, C29.C, C30.2, CLIENT4.GND, HOST4.P$6, JP9.GND1, R23.2, R24.1, R25.1, U13.5, U14.7, U14.18, U14.21, U14.25, U14.26, U15.2
GND5: C31.2, C32.C, C33.2, C34.2, C35.C, C36.2, CLIENT5.GND, HOST5.P$6, JP11.GND1, R28.2, R29.1, R30.1, U16.5, U17.7, U17.18, U17.21, U17.25, U17.26, U18.2
GND6: C37.2, C38.C, C39.2, C40.2, C41.C, C42.2, CLIENT6.GND, HOST6.P$6, JP13.GND1, R33.2, R34.1, R35.1, U19.5, U20.7, U20.18, U20.21, U20.25, U20.26, U21.2
GND7: C43.2, C44.C, C45.2, C46.2, C47.C, C48.2, CLIENT7.GND, HOST7.P$6, JP15.GND1, R38.2, R39.1, R40.1, U22.5, U23.7, U23.18, U23.21, U23.25, U23.26, U24.2
GND8: C49.2, C50.C, C51.2, C52.2, C53.C, C54.2, CLIENT8.GND, HOST8.P$6, JP17.GND1, R43.2, R44.1, R45.1, U25.5, U26.7, U26.18, U26.21, U26.25, U26.26, U27.2
GND9: C55.2, C56.C, C57.2, C58.2, C59.C, C60.2, CLIENT9.GND, HOST9.P$6, JP19.GND1, R48.2, R49.1, R50.1, U28.5, U29.7, U29.18, U29.21, U29.25, U29.26, U30.2
GND10: C61.2, C62.C, C63.2, C64.2, C65.C, C66.2, CLIENT10.GND, HOST10.P$6, JP21.GND1, R53.2, R54.1, R55.1, U31.5, U32.7, U32.18, U32.21, U32.25, U32.26, U33.2
GND11: C67.2, C68.C, C69.2, C70.2, C71.C, C72.2, CLIENT11.GND, HOST11.P$6, JP23.GND1, R58.2, R59.1, R60.1, U34.5, U35.7, U35.18, U35.21, U35.25, U35.26, U36.2
GND12: C73.2, C74.C, C75.2, C76.2, C77.C, C78.2, CLIENT12.GND, HOST12.P$6, JP25.GND1, R63.2, R64.1, R65.1, U37.5, U38.7, U38.18, U38.21, U38.25, U38.26, U39.2
GND13: C79.2, C80.C, C81.2, C82.2, C83.C, C84.2, CLIENT13.GND, HOST13.P$6, JP27.GND1, R68.2, R69.1, R70.1, U40.5, U41.7, U41.18, U41.21, U41.25, U41.26, U42.2
GND14: C85.2, C86.C, C87.2, C88.2, C89.C, C90.2, CLIENT14.GND, HOST14.P$6, JP29.GND1, R73.2, R74.1, R75.1, U43.5, U44.7, U44.18, U44.21, U44.25, U44.26, U45.2
GND15: C91.2, C92.C, C93.2, C94.2, C95.C, C96.2, CLIENT15.GND, HOST15.P$6, JP31.GND1, R78.2, R79.1, R80.1, U46.5, U47.7, U47.18, U47.21, U47.25, U47.26, U48.2
GND16: C97.2, C98.C, C99.2, C100.2, C101.C, C102.2, CLIENT16.GND, HOST16.P$6, JP33.GND1, R83.2, R84.1, R85.1, U49.5, U50.7, U50.18, U50.21, U50.25, U50.26, U51.2
GND17: C103.2, C104.C, C105.2, C106.2, C107.C, C108.2, CLIENT17.GND, HOST17.P$6, JP35.GND1, R88.2, R89.1, R90.1, U52.5, U53.7, U53.18, U53.21, U53.25, U53.26, U54.2
GND18: C109.2, C110.C, C111.2, C112.2, C113.C, C114.2, CLIENT18.GND, HOST18.P$6, JP37.GND1, R93.2, R94.1, R95.1, U55.5, U56.7, U56.18, U56.21, U56.25, U56.26, U57.2
GND19: C115.2, C116.C, C117.2, C118.2, C119.C, C120.2, CLIENT19.GND, HOST19.P$6, JP39.GND1, R98.2, R99.1, R100.1, U58.5, U59.7, U59.18, U59.21, U59.25, U59.26, U60.2
GND20: C121.2, C122.C, C123.2, C124.2, C125.C, C126.2, CLIENT20.GND, HOST20.P$6, JP41.GND1, R103.2, R104.1, R105.1, U61.5, U62.7, U62.18, U62.21, U62.25, U62.26, U63.2
GND21: C127.2, C128.C, C129.2, C130.2, C131.C, C132.2, CLIENT21.GND, HOST21.P$6, JP43.GND1, R108.2, R109.1, R110.1, U64.5, U65.7, U65.18, U65.21, U65.25, U65.26, U66.2
GND22: C133.2, C134.C, C135.2, C136.2, C137.C, C138.2, CLIENT22.GND, HOST22.P$6, JP45.GND1, R113.2, R114.1, R115.1, U67.5, U68.7, U68.18, U68.21, U68.25, U68.26, U69.2
GND23: C139.2, C140.C, C141.2, C142.2, C143.C, C144.2, CLIENT23.GND, HOST23.P$6, JP47.GND1, R118.2, R119.1, R120.1, U70.5, U71.7, U71.18, U71.21, U71.25, U71.26, U72.2
GND24: C145.2, C146.C, C147.2, C148.2, C149.C, C150.2, CLIENT24.GND, HOST24.P$6, JP49.GND1, R123.2, R124.1, R125.1, U73.5, U74.7, U74.18, U74.21, U74.25, U74.26, U75.2
GND25: C151.2, C152.C, C153.2, C154.2, C155.C, C156.2, CLIENT25.GND, HOST25.P$6, JP51.GND1, R128.2, R129.1, R130.1, U76.5, U77.7, U77.18, U77.21, U77.25, U77.26, U78.2
GND26: C157.2, C158.C, C159.2, C160.2, C161.C, C162.2, CLIENT26.GND, HOST26.P$6, JP53.GND1, R133.2, R134.1, R135.1, U79.5, U80.7, U80.18, U80.21, U80.25, U80.26, U81.2
GND27: C163.2, C164.C, C165.2, C166.2, C167.C, C168.2, CLIENT27.GND, HOST27.P$6, JP55.GND1, R138.2, R139.1, R140.1, U82.5, U83.7, U83.18, U83.21, U83.25, U83.26, U84.2
GND28: C169.2, C170.C, C171.2, C172.2, C173.C, C174.2, CLIENT28.GND, HOST28.P$6, JP57.GND1, R143.2, R144.1, R145.1, U85.5, U86.7, U86.18, U86.21, U86.25, U86.26, U87.2
GND29: C175.2, C176.C, C177.2, C178.2, C179.C, C180.2, CLIENT29.GND, HOST29.P$6, JP59.GND1, R148.2, R149.1, R150.1, U88.5, U89.7, U89.18, U89.21, U89.25, U89.26, U90.2
GND30: C181.2, C182.C, C183.2, C184.2, C185.C, C186.2, CLIENT30.GND, HOST30.P$6, JP61.GND1, R153.2, R154.1, R155.1, U91.5, U92.7, U92.18, U92.21, U92.25, U92.26, U93.2
GND31: C187.2, C188.C, C189.2, C190.2, C191.C, C192.2, CLIENT31.GND, HOST31.P$6, JP63.GND1, R158.2, R159.1, R160.1, U94.5, U95.7, U95.18, U95.21, U95.25, U95.26, U96.2
GND32: C193.2, C194.C, C195.2, C196.2, C197.C, C198.2, CLIENT32.GND, HOST32.P$6, JP65.GND1, R163.2, R164.1, R165.1, U97.5, U98.7, U98.18, U98.21, U98.25, U98.26, U99.2
GND33: C199.2, C200.C, C201.2, C202.2, C203.C, C204.2, CLIENT33.GND, HOST33.P$6, JP67.GND1, R168.2, R169.1, R170.1, U100.5, U101.7, U101.18, U101.21, U101.25, U101.26, U102.2
GND34: C205.2, C206.C, C207.2, C208.2, C209.C, C210.2, CLIENT34.GND, HOST34.P$6, JP69.GND1, R173.2, R174.1, R175.1, U103.5, U104.7, U104.18, U104.21, U104.25, U104.26, U105.2
GND35: C211.2, C212.C, C213.2, C214.2, C215.C, C216.2, CLIENT35.GND, HOST35.P$6, JP71.GND1, R178.2, R179.1, R180.1, U106.5, U107.7, U107.18, U107.21, U107.25, U107.26, U108.2
GND36: C217.2, C218.C, C219.2, C220.2, C221.C, C222.2, CLIENT36.GND, HOST36.P$6, JP73.GND1, R183.2, R184.1, R185.1, U109.5, U110.7, U110.18, U110.21, U110.25, U110.26, U111.2
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
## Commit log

2014-05-19 Incorporate changes from review
2014-06-24 2nd round protos - add vias to strain relief pads on connector - flip the client connector - remove the USB indicator LED and change other LED label - change silk from JP1 and JP3 to HOST and CLIENT
2014-06-24 Minor changes from review
2014-07-18 Ready for review for reds
2014-07-21 Ready for release.
2014-07-24 added local fiducials
2014-07-24 created panels
    both regular, and giant
2014-07-29 Add Fritzing files
2014-08-21 Fixed bottom silk, rev to 11
2014-08-21 re-created panel with correct silk
2014-08-21 changed file name to v11
2014-09-25 Add an example
